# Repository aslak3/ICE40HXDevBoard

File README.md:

# ICE40HXDevBoard: an expandable iCE40HX4K development board

## Features

The specification for this development board is as follows:

* [iCE40HX4K](https://www.latticesemi.com/view_document?document_id=49312) in
144 pin QFP
  * [N25Q032A](https://docs.rs-online.com/0866/0900766b80f7f8ab.pdf) 32 Mbit SPI flash
* Space for two 5mm x 3mm oscillators
* [W9825G6KH](https://www.mouser.co.uk/datasheet/2/949/w9825g6kh_a04-1489735.pdf) 4M x 4 Banks x 16 bits SDRAM (32 MByte)
* PS/2 port with two channels for a mouse and keyboard
* I2C:
  * [DS3231M](https://www.analog.com/media/en/technical-documentation/data-sheets/ds3231m.pdf) RTC
  * [AT24C64](https://ww1.microchip.com/downloads/en/devicedoc/doc0336.pdf) EEPROM
  * Header for I2C connections
* RGB LED
* 4 buttons
* Buzzer
* [FT231XS](https://ftdichip.com/wp-content/uploads/2024/05/DS_FT231X.pdf) USB to UART converter with USB-C socket doubling up as the source of 5V power
* [MicroSDCard](https://en.wikipedia.org/wiki/SD_card) slot
* [PMOD](https://en.wikipedia.org/wiki/Pmod_Interface) header
* 40 pin expansion:
  * 3.3V and 5V power, 27 general purpose IO, 2 clock pins, shared I2C bus

A [schematic](ICE40HXDevBoard.pdf) is included here, along with the
[KiCAD](https://www.kicad.org) data files, whcih are in KiCAD 6 format.

## HDMI expansion card features

An expansion card featuring HDMI and I2S output on a 3.5mm jack has been built:

* [TFP410PAP](https://www.ti.com/lit/ds/symlink/tfp410.pdf) HDMI transmitter
  * Full size HDMI connector
* [PCM5100A](https://www.ti.com/lit/ds/symlink/pcm5100a.pdf) I2S DAC
  * 3.5mm stereo jack

## VGA expansion card features

A further, unbuilt, expansion card has been designed for VGA output:

* [ADV7123](https://www.analog.com/media/en/technical-documentation/data-sheets/ADV7123.pdf) RGB DAC
* [PCM5100A](https://www.ti.com/lit/ds/symlink/pcm5100a.pdf) I2S DAC
  * 3.5mm stereo jack

## PCB design

The PCBs are 4 layer boards.  My boards were manufactured by
[JLCPCB](https://www.jlcpcb.com).

## Using

The jumper mechanism to route the SPI signals which carry the configuration data
from the programmer was borrowed directly from the [Lattice’s iCE40 UltraPlus
Breakout Board](https://www.latticesemi.com/view_document?document_id=51987).

Any iCE40 compatible programmer should be useable. I built my own, out of a Pi
Pico, the software for which is documented in [another
repo](https://github.com/aslak3/spi-flasher). The programmer has been used to
program both the attached flash and the FPGA directly.

The header is a IDC10 in 100mil pitch. For the pinout refer to the schematic.

## Possible gotchas

The design of the FPGA board is a tweaked version of the build I have on my bench, since it has some issues:

* The PMOD pinning was backwards.
* The PS/2 port lacked clamping diodes due to the FPGA's intolerance of 5V signals from the PS/2 device. Remarkably I see no problems with my board, but it is not correct not having diodes to clamp the PS/2 data and clock lines to 3.3V.

The following features have not been tested yet:

* The MicroSDCard slot
* The SDRAM
* The I2C RTC
* The I2S DAC

## Blog

The best place to learn about this board is undoubtably [my
blog](https://www.aslak.net/).

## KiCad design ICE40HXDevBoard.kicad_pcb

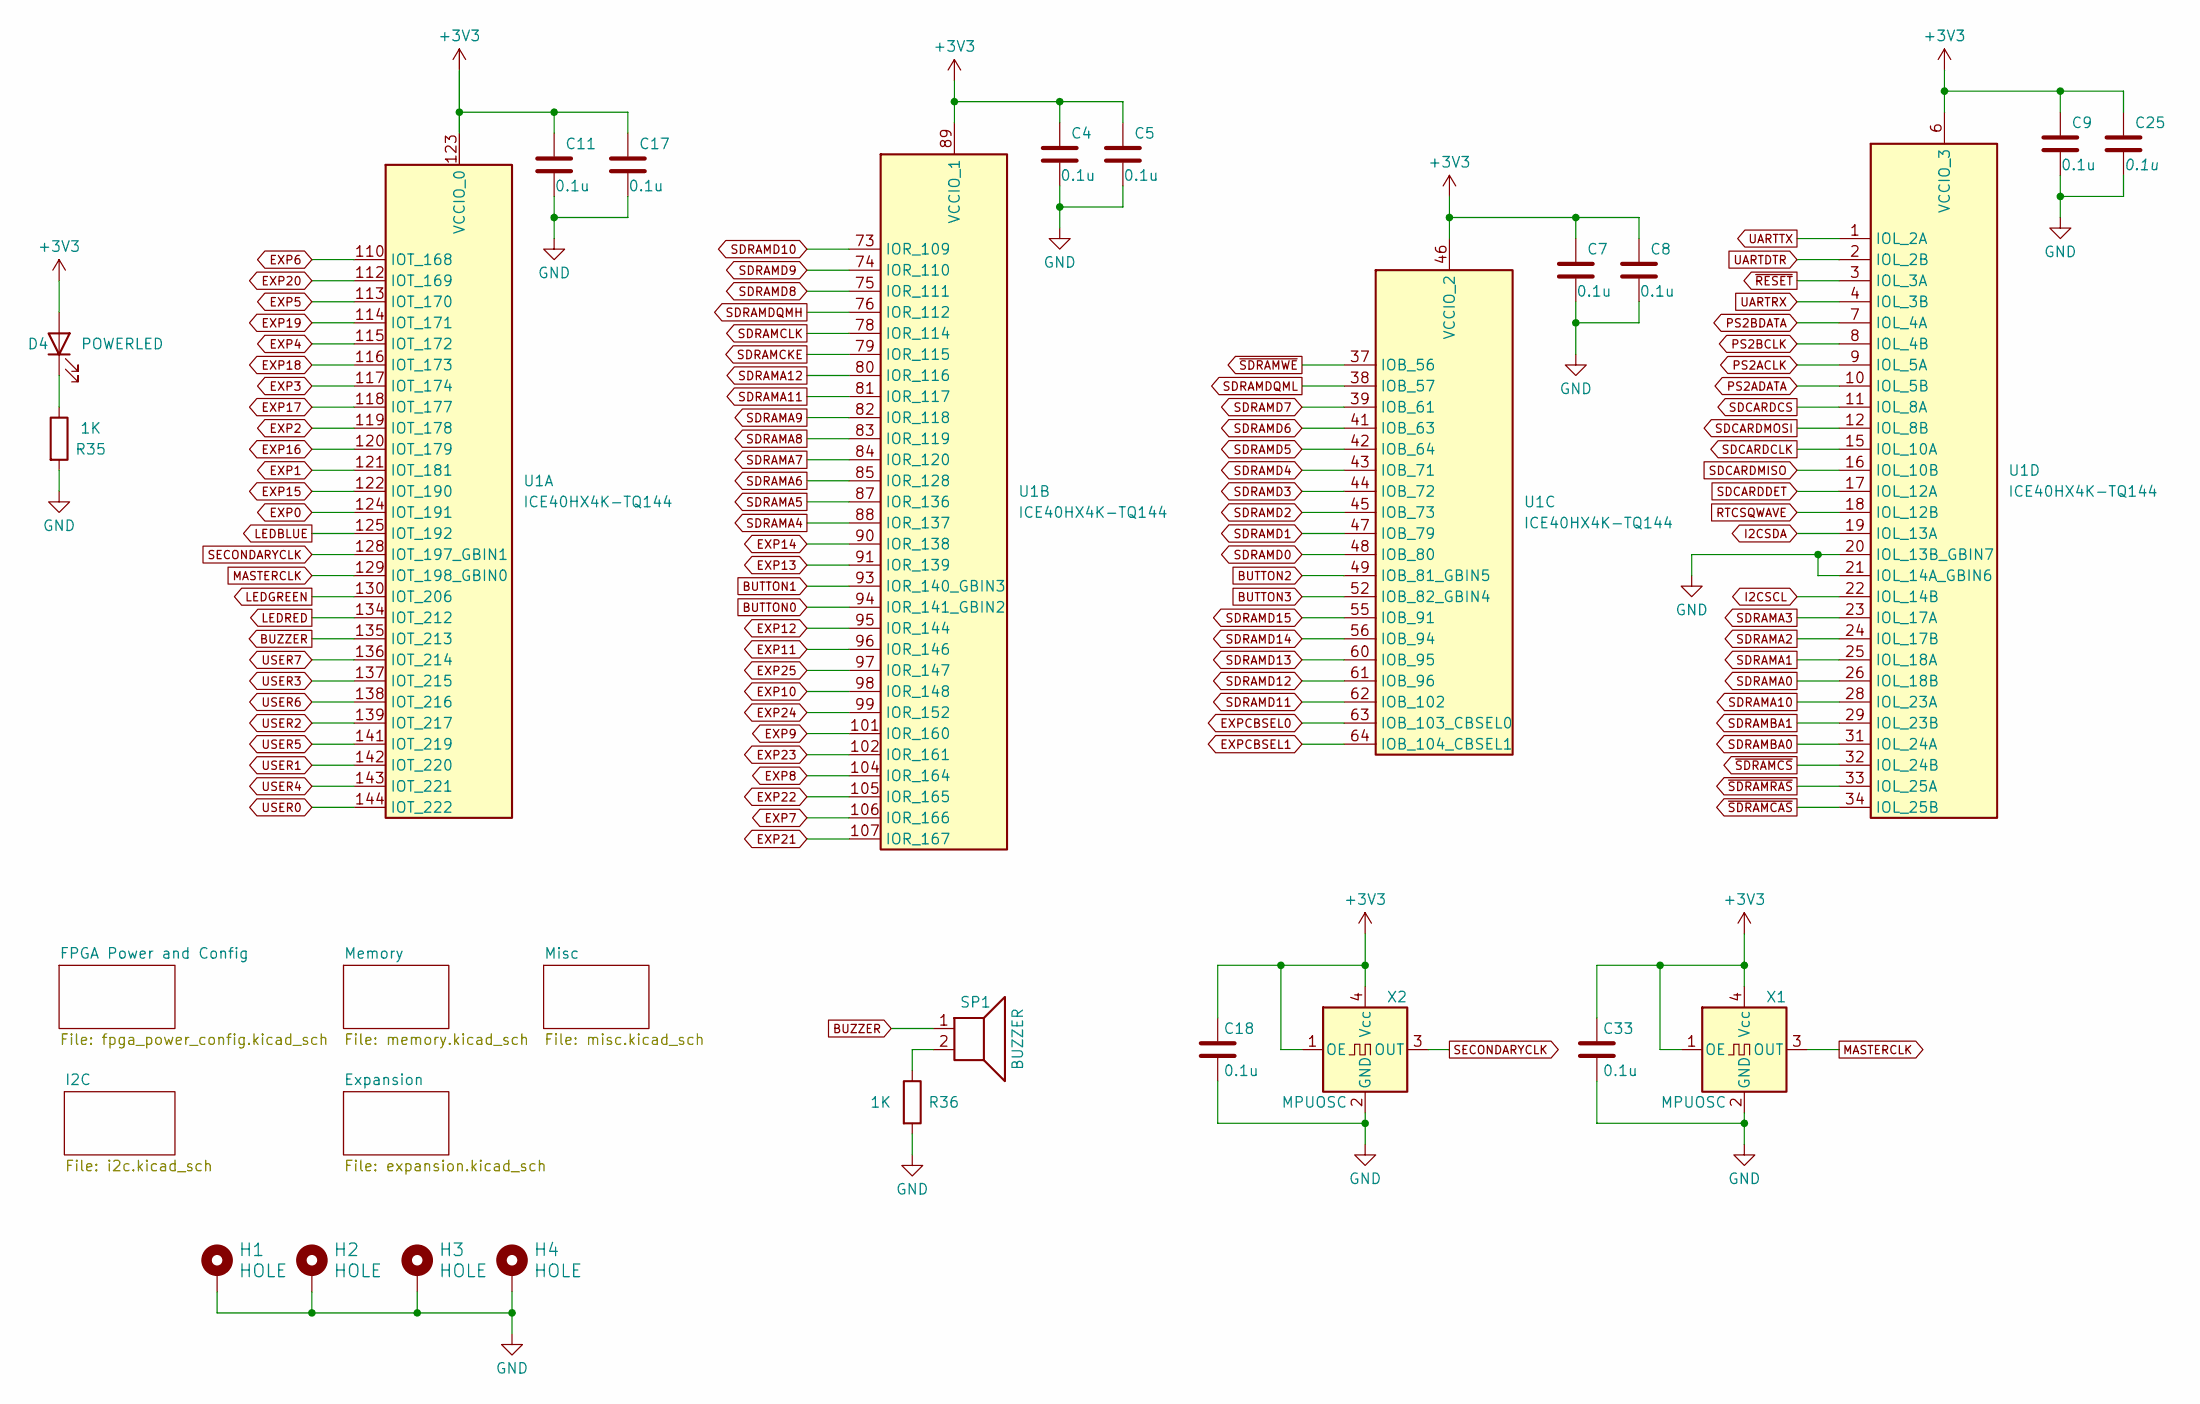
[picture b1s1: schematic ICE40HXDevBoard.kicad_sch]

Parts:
C4, C5, C7, C8, C9, C11, C17, C18, C25, C33: 0.1u; C_0805_2012Metric
D4: POWERLED; LED_1210_3225Metric
H1, H2, H3, H4: HOLE; MountingHole_3.2mm_M3_Pad
R35, R36: 1K; R_0805_2012Metric
SP1: BUZZER; Buzzer_15x7.5RM7.6
U1: ICE40HX4K-TQ144; TQFP-144_20x20mm_P0.5mm
X1, X2: MPUOSC; Oscillator_SMD_SeikoEpson_SG8002LB-4Pin_5.0x3.2mm

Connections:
+3V3: C4.1, C5.1, C7.1, C8.1, C9.1, C11.1, C17.1, C18.1, C25.1, C33.1, D4.2 (A), U1.6 (VCCIO_3), U1.30 (VCCIO_3), U1.46 (VCCIO_2), U1.57 (VCCIO_2), U1.89 (VCCIO_1), U1.100 (VCCIO_1), U1.123 (VCCIO_0), U1.131 (VCCIO_0), X1.1 (OE), X1.4 (Vcc), X2.1 (OE), X2.4 (Vcc); also elsewhere on the board
BUTTON0: U1.94 (IOR_141_GBIN2); also elsewhere on the board
BUTTON1: U1.93 (IOR_140_GBIN3); also elsewhere on the board
BUTTON2: U1.49 (IOB_81_GBIN5); also elsewhere on the board
BUTTON3: U1.52 (IOB_82_GBIN4); also elsewhere on the board
BUZZER: SP1.1, U1.135 (IOT_213)
EXP0: U1.124 (IOT_191); also elsewhere on the board
EXP1: U1.121 (IOT_181); also elsewhere on the board
EXP2: U1.119 (IOT_178); also elsewhere on the board
EXP3: U1.117 (IOT_174); also elsewhere on the board
EXP4: U1.115 (IOT_172); also elsewhere on the board
EXP5: U1.113 (IOT_170); also elsewhere on the board
EXP6: U1.110 (IOT_168); also elsewhere on the board
EXP7: U1.106 (IOR_166); also elsewhere on the board
EXP8: U1.104 (IOR_164); also elsewhere on the board
EXP9: U1.101 (IOR_160); also elsewhere on the board
EXP10: U1.98 (IOR_148); also elsewhere on the board
EXP11: U1.96 (IOR_146); also elsewhere on the board
EXP12: U1.95 (IOR_144); also elsewhere on the board
EXP13: U1.91 (IOR_139); also elsewhere on the board
EXP14: U1.90 (IOR_138); also elsewhere on the board
EXP15: U1.122 (IOT_190); also elsewhere on the board
EXP16: U1.120 (IOT_179); also elsewhere on the board
EXP17: U1.118 (IOT_177); also elsewhere on the board
EXP18: U1.116 (IOT_173); also elsewhere on the board
EXP19: U1.114 (IOT_171); also elsewhere on the board
EXP20: U1.112 (IOT_169); also elsewhere on the board
EXP21: U1.107 (IOR_167); also elsewhere on the board
EXP22: U1.105 (IOR_165); also elsewhere on the board
EXP23: U1.102 (IOR_161); also elsewhere on the board
EXP24: U1.99 (IOR_152); also elsewhere on the board
EXP25: U1.97 (IOR_147); also elsewhere on the board
EXPCBSEL0: U1.63 (IOB_103_CBSEL0); also elsewhere on the board
EXPCBSEL1: U1.64 (IOB_104_CBSEL1); also elsewhere on the board
GND: C4.2, C5.2, C7.2, C8.2, C9.2, C11.2, C17.2, C18.2, C25.2, C33.2, H1.1, H2.1, H3.1, H4.1, R35.2, R36.2, U1.20 (IOL_13B_GBIN7), U1.21 (IOL_14A_GBIN6), X1.2 (GND), X2.2 (GND); also elsewhere on the board
I2CSCL: U1.22 (IOL_14B); also elsewhere on the board
I2CSDA: U1.19 (IOL_13A); also elsewhere on the board
LEDBLUE: U1.125 (IOT_192); also elsewhere on the board
LEDGREEN: U1.130 (IOT_206); also elsewhere on the board
LEDRED: U1.134 (IOT_212); also elsewhere on the board
MASTERCLK: U1.129 (IOT_198_GBIN0), X1.3 (OUT); also elsewhere on the board
unnamed: D4.1 (K), R35.1
unnamed: R36.1, SP1.2
PS2ACLK: U1.9 (IOL_5A); also elsewhere on the board
PS2ADATA: U1.10 (IOL_5B); also elsewhere on the board
PS2BCLK: U1.8 (IOL_4B); also elsewhere on the board
PS2BDATA: U1.7 (IOL_4A); also elsewhere on the board
RTCSQWAVE: U1.18 (IOL_12B); also elsewhere on the board
SDCARDCLK: U1.15 (IOL_10A); also elsewhere on the board
SDCARDCS: U1.11 (IOL_8A); also elsewhere on the board
SDCARDDET: U1.17 (IOL_12A); also elsewhere on the board
SDCARDMISO: U1.16 (IOL_10B); also elsewhere on the board
SDCARDMOSI: U1.12 (IOL_8B); also elsewhere on the board
SDRAMA0: U1.26 (IOL_18B); also elsewhere on the board
SDRAMA1: U1.25 (IOL_18A); also elsewhere on the board
SDRAMA2: U1.24 (IOL_17B); also elsewhere on the board
SDRAMA3: U1.23 (IOL_17A); also elsewhere on the board
SDRAMA4: U1.88 (IOR_137); also elsewhere on the board
SDRAMA5: U1.87 (IOR_136); also elsewhere on the board
SDRAMA6: U1.85 (IOR_128); also elsewhere on the board
SDRAMA7: U1.84 (IOR_120); also elsewhere on the board
SDRAMA8: U1.83 (IOR_119); also elsewhere on the board
SDRAMA9: U1.82 (IOR_118); also elsewhere on the board
SDRAMA10: U1.28 (IOL_23A); also elsewhere on the board
SDRAMA11: U1.81 (IOR_117); also elsewhere on the board
SDRAMA12: U1.80 (IOR_116); also elsewhere on the board
SDRAMBA0: U1.31 (IOL_24A); also elsewhere on the board
SDRAMBA1: U1.29 (IOL_23B); also elsewhere on the board
SDRAMCKE: U1.79 (IOR_115); also elsewhere on the board
SDRAMCLK: U1.78 (IOR_114); also elsewhere on the board
SDRAMD0: U1.48 (IOB_80); also elsewhere on the board
SDRAMD1: U1.47 (IOB_79); also elsewhere on the board
SDRAMD2: U1.45 (IOB_73); also elsewhere on the board
SDRAMD3: U1.44 (IOB_72); also elsewhere on the board
SDRAMD4: U1.43 (IOB_71); also elsewhere on the board
SDRAMD5: U1.42 (IOB_64); also elsewhere on the board
SDRAMD6: U1.41 (IOB_63); also elsewhere on the board
SDRAMD7: U1.39 (IOB_61); also elsewhere on the board
SDRAMD8: U1.75 (IOR_111); also elsewhere on the board
SDRAMD9: U1.74 (IOR_110); also elsewhere on the board
SDRAMD10: U1.73 (IOR_109); also elsewhere on the board
SDRAMD11: U1.62 (IOB_102); also elsewhere on the board
SDRAMD12: U1.61 (IOB_96); also elsewhere on the board
SDRAMD13: U1.60 (IOB_95); also elsewhere on the board
SDRAMD14: U1.56 (IOB_94); also elsewhere on the board
SDRAMD15: U1.55 (IOB_91); also elsewhere on the board
SDRAMDQMH: U1.76 (IOR_112); also elsewhere on the board
SDRAMDQML: U1.38 (IOB_57); also elsewhere on the board
SECONDARYCLK: U1.128 (IOT_197_GBIN1), X2.3 (OUT); also elsewhere on the board
UARTDTR: U1.2 (IOL_2B); also elsewhere on the board
UARTRX: U1.4 (IOL_3B); also elsewhere on the board
UARTTX: U1.1 (IOL_2A); also elsewhere on the board
USER0: U1.144 (IOT_222); also elsewhere on the board
USER1: U1.142 (IOT_220); also elsewhere on the board
USER2: U1.139 (IOT_217); also elsewhere on the board
USER3: U1.137 (IOT_215); also elsewhere on the board
USER4: U1.143 (IOT_221); also elsewhere on the board
USER5: U1.141 (IOT_219); also elsewhere on the board
USER6: U1.138 (IOT_216); also elsewhere on the board
USER7: U1.136 (IOT_214); also elsewhere on the board
~RESET: U1.3 (IOL_3A); also elsewhere on the board
~SDRAMCAS: U1.34 (IOL_25B); also elsewhere on the board
~SDRAMCS: U1.32 (IOL_24B); also elsewhere on the board
~SDRAMRAS: U1.33 (IOL_25A); also elsewhere on the board
~SDRAMWE: U1.37 (IOB_56); also elsewhere on the board

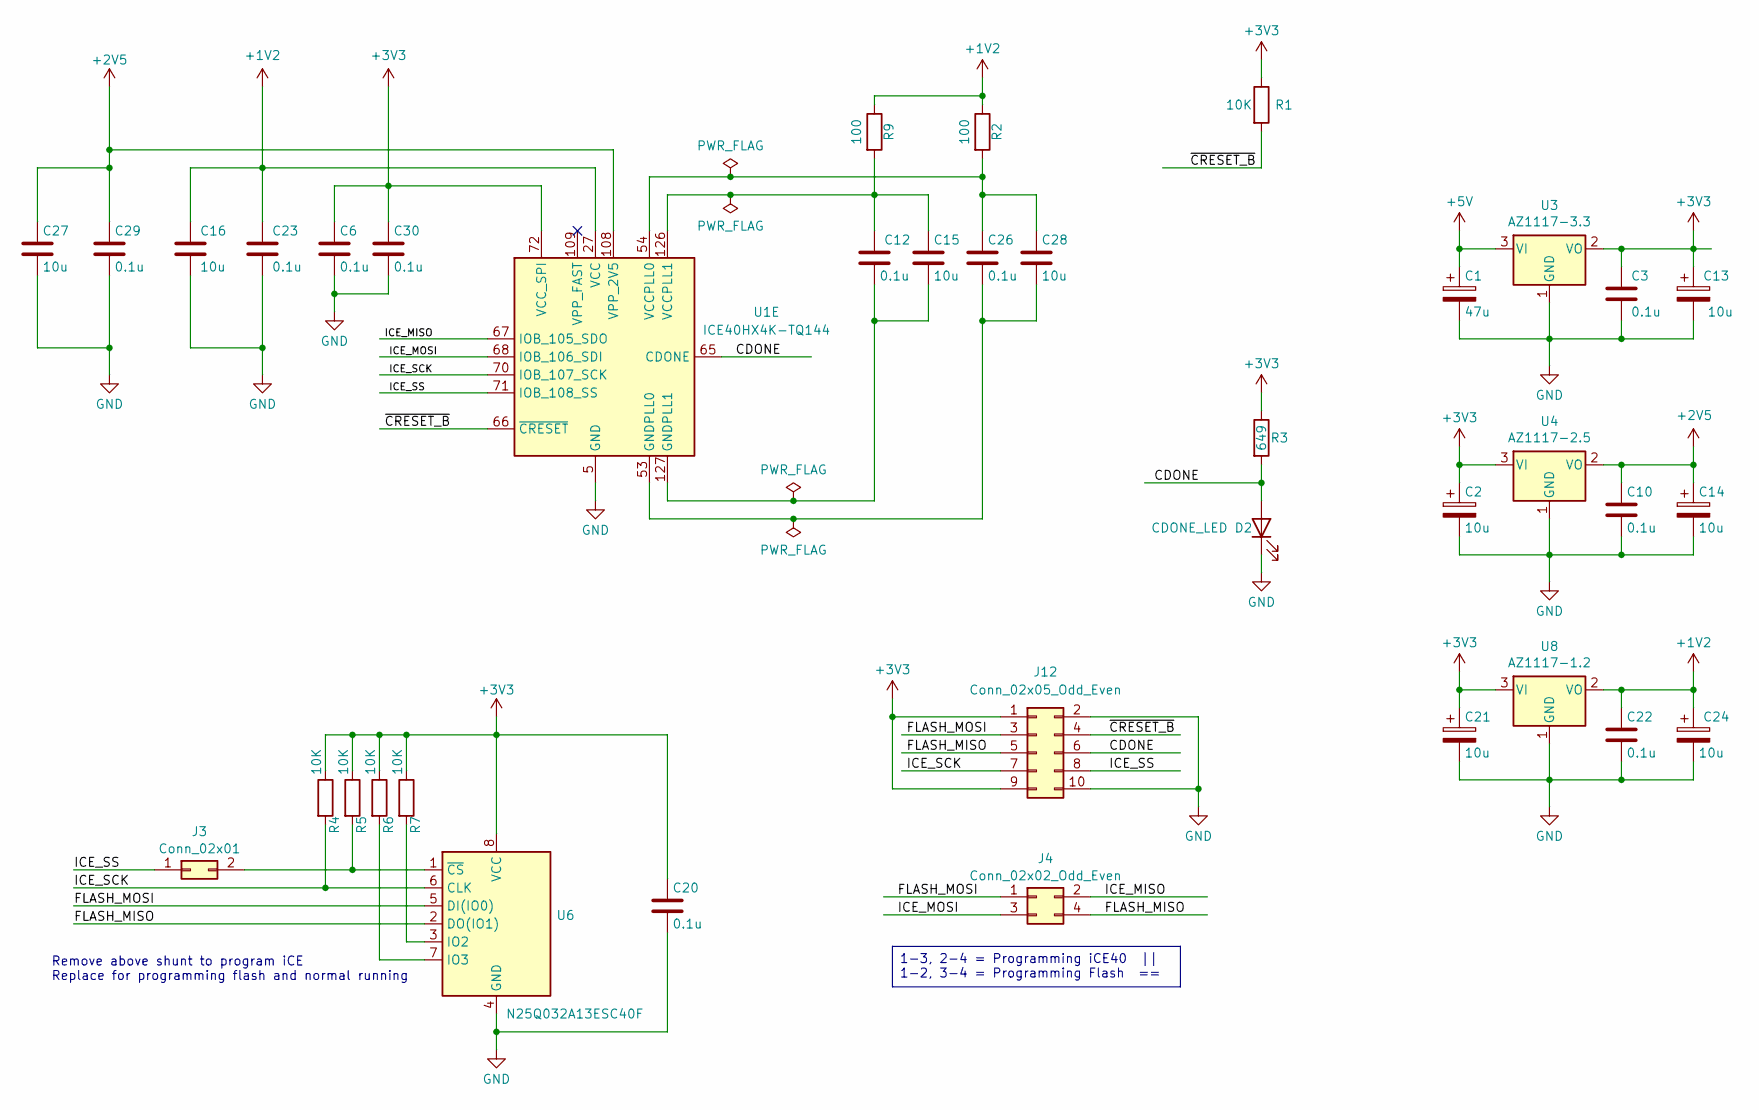
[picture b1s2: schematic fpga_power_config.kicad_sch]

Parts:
C1: 47u; CP_EIA-7343-15_Kemet-W
C2, C13, C14, C21, C24: 10u; CP_EIA-3216-10_Kemet-I
C3, C6, C10, C12, C20, C22, C23, C26, C29, C30: 0.1u; C_0805_2012Metric
C15, C16, C27, C28: 10u; C_0805_2012Metric
D2: CDONE_LED; LED_1210_3225Metric
J3: Conn_02x01; PinHeader_2x01_P2.54mm_Vertical
J4: Conn_02x02_Odd_Even; PinHeader_2x02_P2.54mm_Vertical
J12: Conn_02x05_Odd_Even; IDC-Header_2x05_P2.54mm_Vertical
R1, R4, R5, R6, R7: 10K; R_0805_2012Metric
R2, R9: 100; R_0805_2012Metric
R3: 649; R_0805_2012Metric
U1: ICE40HX4K-TQ144; TQFP-144_20x20mm_P0.5mm
U3: AZ1117-3.3; SOT-223-3_TabPin2
U4: AZ1117-2.5; SOT-223-3_TabPin2
U6: N25Q032A13ESC40F; SOP-8_3.9x4.9mm_P1.27mm
U8: AZ1117-1.2; SOT-223-3_TabPin2

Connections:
+1V2: C16.1, C22.1, C23.1, C24.1, R2.1, R9.1, U1.27 (VCC), U1.40 (VCC), U1.92 (VCC), U1.111 (VCC), U8.2 (VO)
+2V5: C10.1, C14.1, C27.1, C29.1, U1.108 (VPP_2V5), U4.2 (VO)
+3V3: C2.1, C3.1, C6.1, C13.1, C20.1, C21.1, C30.1, J12.1, J12.9, R1.1, R3.1, R4.1, R5.1, R6.1, R7.1, U1.72 (VCC_SPI), U3.2 (VO), U4.3 (VI), U6.8 (VCC), U8.3 (VI); also elsewhere on the board
+5V: C1.1, U3.3 (VI); also elsewhere on the board
/FPGA Power and Config/CDONE: D2.2 (A), J12.6, R3.2, U1.65 (CDONE)
/FPGA Power and Config/FLASH_MISO: J4.4, J12.5, U6.2 (DO(IO1))
/FPGA Power and Config/FLASH_MOSI: J4.1, J12.3, U6.5 (DI(IO0))
/FPGA Power and Config/ICE_MISO: J4.2, U1.67 (IOB_105_SDO)
/FPGA Power and Config/ICE_MOSI: J4.3, U1.68 (IOB_106_SDI)
/FPGA Power and Config/ICE_SCK: J12.7, R4.2, U1.70 (IOB_107_SCK), U6.6 (CLK)
/FPGA Power and Config/ICE_SS: J3.1, J12.8, U1.71 (IOB_108_SS)
/FPGA Power and Config/~CRESET_B: J12.4, R1.2, U1.66 (~CRESET)
GND: C1.2, C2.2, C3.2, C6.2, C10.2, C13.2, C14.2, C16.2, C20.2, C21.2, C22.2, C23.2, C24.2, C27.2, C29.2, C30.2, D2.1 (K), J12.2, J12.10, U1.5 (GND), U1.13 (GND), U1.14 (GND), U1.59 (GND), U1.69 (GND), U1.86 (GND), U1.103 (GND), U1.132 (GND), U1.140 (GND), U3.1 (GND), U4.1 (GND), U6.4 (GND), U8.1 (GND); also elsewhere on the board
unnamed: J3.2, R5.2, U6.1 (~CS)
unnamed: C26.2, C28.2, U1.53 (GNDPLL0)
unnamed: C12.2, C15.2, U1.127 (GNDPLL1)
unnamed: C26.1, C28.1, R2.2, U1.54 (VCCPLL0)
unnamed: C12.1, C15.1, R9.2, U1.126 (VCCPLL1)
unnamed: R7.2, U6.3 (IO2)
unnamed: R6.2, U6.7 (IO3)

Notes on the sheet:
Remove above shunt to program iCE Replace for programming flash and normal running
1-3, 2-4 = Programming iCE40 || 1-2, 3-4 = Programming Flash ==

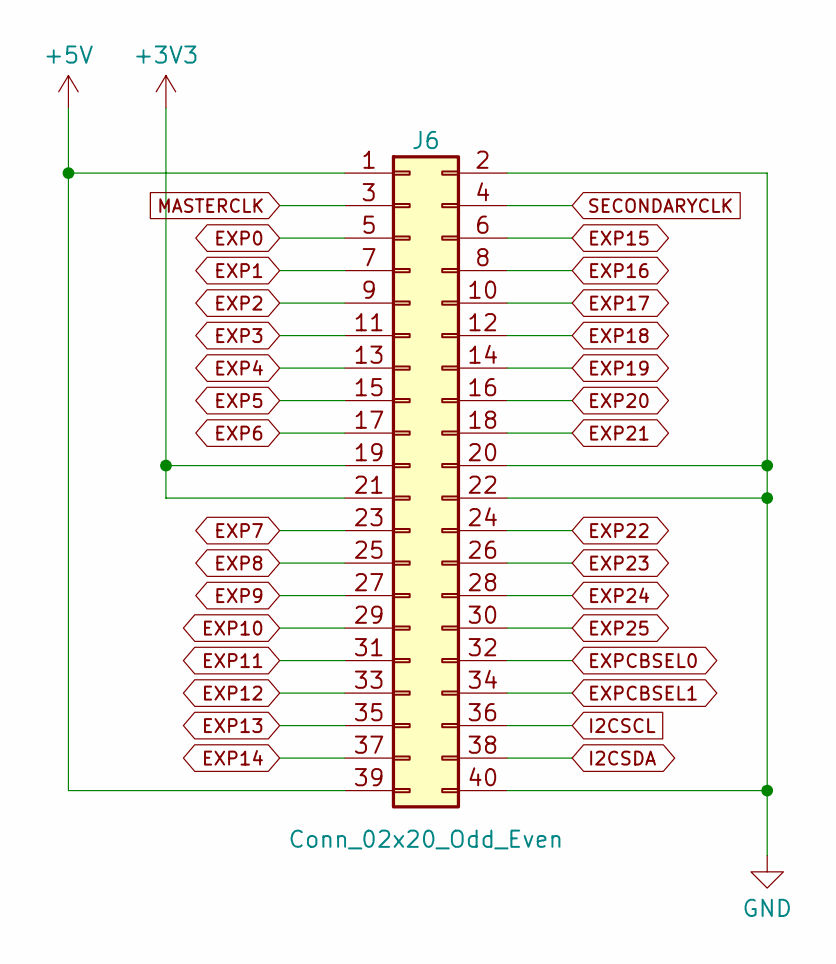
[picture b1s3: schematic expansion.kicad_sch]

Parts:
J6: Conn_02x20_Odd_Even; PinHeader_2x20_P2.54mm_Horizontal

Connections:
+3V3: J6.19, J6.21; also elsewhere on the board
+5V: J6.1, J6.39; also elsewhere on the board
EXP0: J6.5; also elsewhere on the board
EXP1: J6.7; also elsewhere on the board
EXP2: J6.9; also elsewhere on the board
EXP3: J6.11; also elsewhere on the board
EXP4: J6.13; also elsewhere on the board
EXP5: J6.15; also elsewhere on the board
EXP6: J6.17; also elsewhere on the board
EXP7: J6.23; also elsewhere on the board
EXP8: J6.25; also elsewhere on the board
EXP9: J6.27; also elsewhere on the board
EXP10: J6.29; also elsewhere on the board
EXP11: J6.31; also elsewhere on the board
EXP12: J6.33; also elsewhere on the board
EXP13: J6.35; also elsewhere on the board
EXP14: J6.37; also elsewhere on the board
EXP15: J6.6; also elsewhere on the board
EXP16: J6.8; also elsewhere on the board
EXP17: J6.10; also elsewhere on the board
EXP18: J6.12; also elsewhere on the board
EXP19: J6.14; also elsewhere on the board
EXP20: J6.16; also elsewhere on the board
EXP21: J6.18; also elsewhere on the board
EXP22: J6.24; also elsewhere on the board
EXP23: J6.26; also elsewhere on the board
EXP24: J6.28; also elsewhere on the board
EXP25: J6.30; also elsewhere on the board
EXPCBSEL0: J6.32; also elsewhere on the board
EXPCBSEL1: J6.34; also elsewhere on the board
GND: J6.2, J6.20, J6.22, J6.40; also elsewhere on the board
I2CSCL: J6.36; also elsewhere on the board
I2CSDA: J6.38; also elsewhere on the board
MASTERCLK: J6.3; also elsewhere on the board
SECONDARYCLK: J6.4; also elsewhere on the board

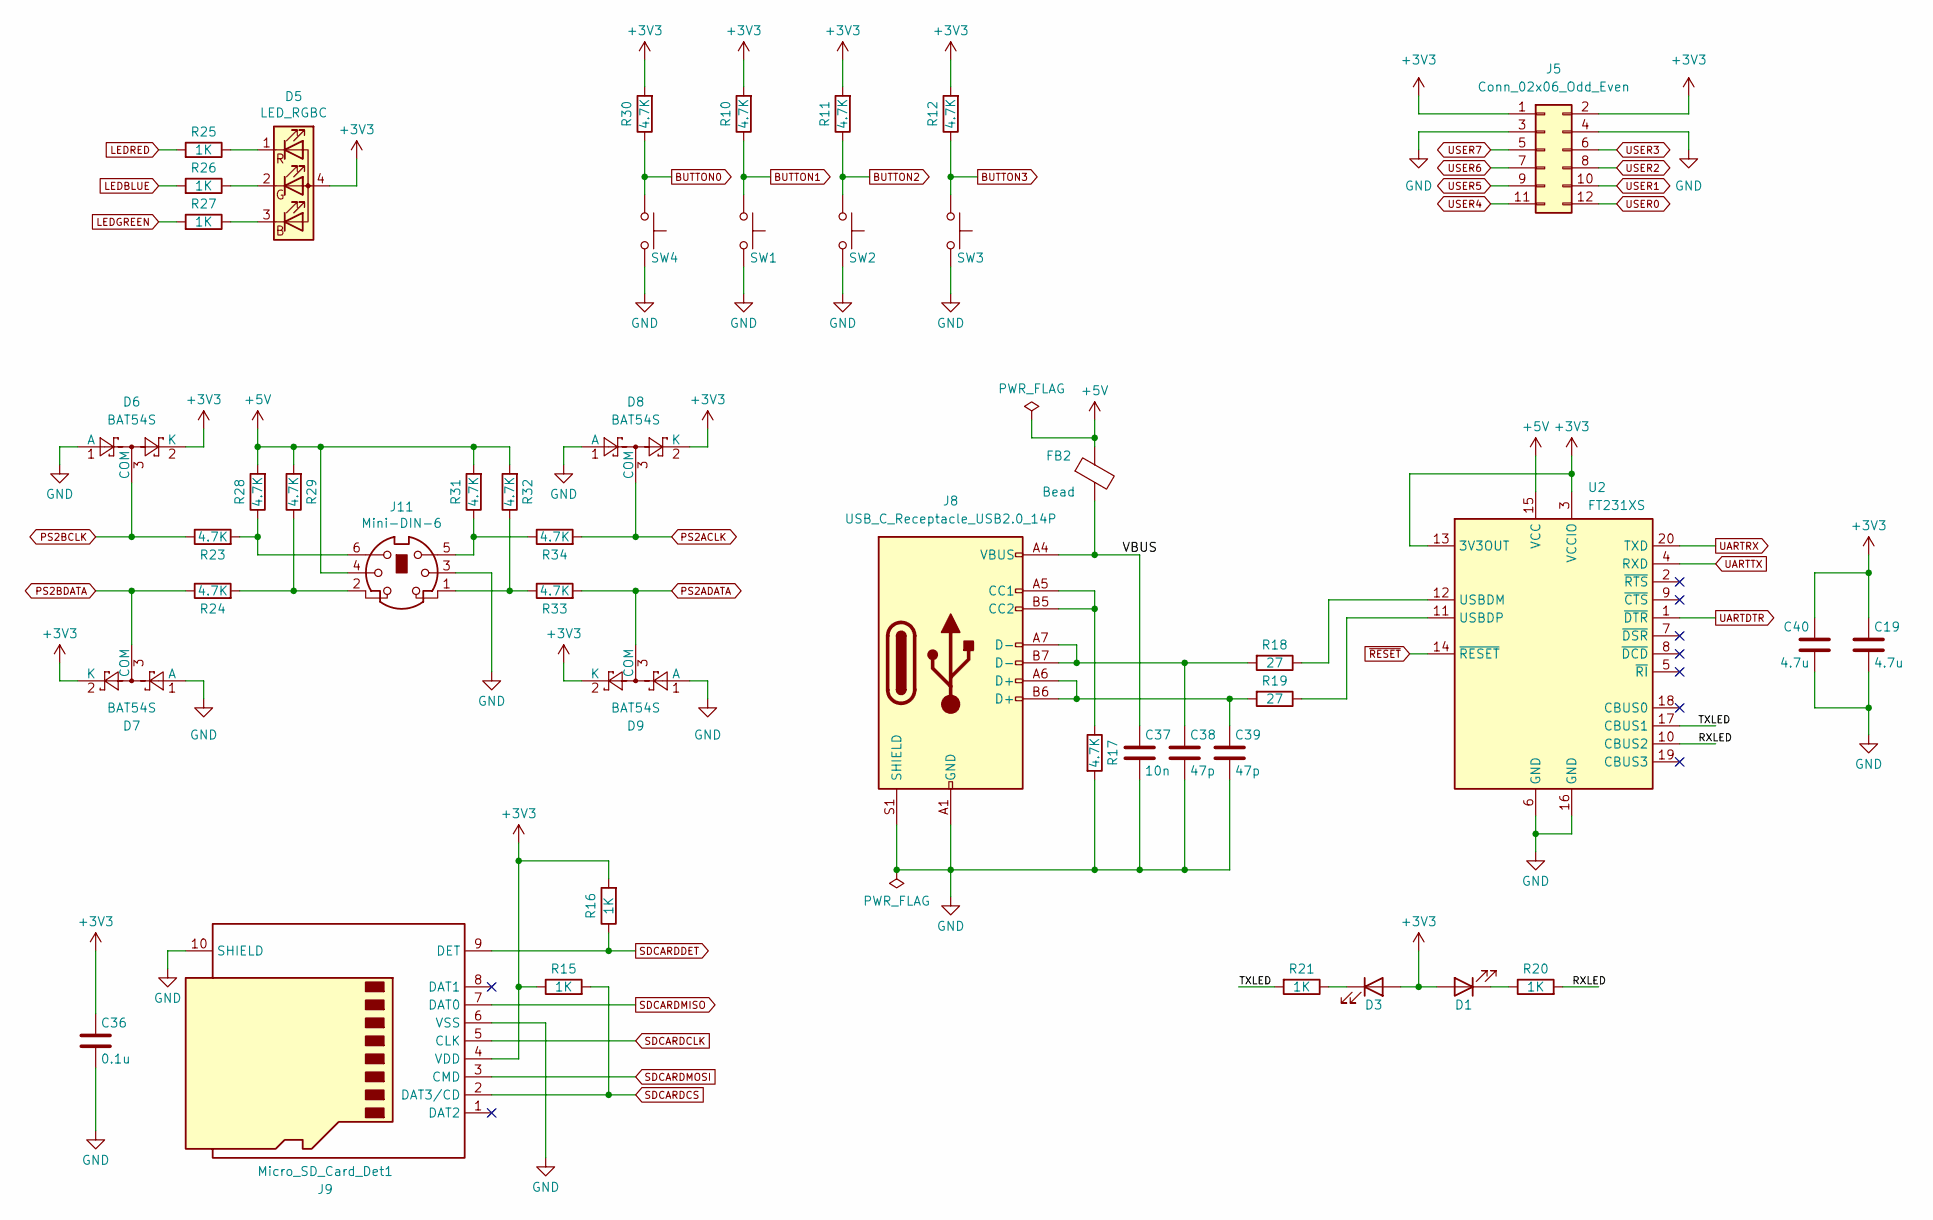
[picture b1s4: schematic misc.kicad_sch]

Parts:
C19, C40: 4.7u; C_0805_2012Metric
C36: 0.1u; C_0805_2012Metric
C37: 10n; C_0805_2012Metric
C38, C39: 47p; C_0805_2012Metric
D1, D3: UART_LED; LED_1210_3225Metric
D5: LED_RGBC; LED_Cree-PLCC4_3.2x2.8mm_CCW
D6, D7, D8, D9: BAT54S; SOT-23
FB2: Bead; L_1206_3216Metric
J5: Conn_02x06_Odd_Even; PinSocket_2x06_P2.54mm_Horizontal
J8: USB_C_Receptacle_USB2.0_14P; USB_C_Receptacle_GCT_USB4105-xx-A_16P_TopMnt_Horizontal
J9: Micro_SD_Card_Det1; microSD_HC_Hirose_DM3BT-DSF-PEJS
J11: Mini-DIN-6; Connector_Mini-DIN_Female_6Pin_2rows
R10, R11, R12, R17, R23, R24, R28, R29, R30, R31, R32, R33, R34: 4.7K; R_0805_2012Metric
R15, R16, R20, R21, R25, R26, R27: 1K; R_0805_2012Metric
R18, R19: 27; R_0805_2012Metric
SW1, SW2, SW3, SW4: BUTTON; SW_Push_1P1T_NO_CK_KSC6xxJ
U2: FT231XS; SSOP-20_3.9x8.7mm_P0.635mm

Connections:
+3V3: C19.1, C36.1, C40.1, D1.2 (A), D3.2 (A), D5.4 (A), D6.2 (K), D7.2 (K), D8.2 (K), D9.2 (K), J5.1, J5.2, J9.4 (VDD), R10.2, R11.2, R12.2, R15.1, R16.2, R30.2, U2.3 (VCCIO), U2.13 (3V3OUT); also elsewhere on the board
+5V: FB2.1, J11.4, R28.2, R29.2, R31.2, R32.2, U2.15 (VCC); also elsewhere on the board
/Misc/RXLED: R20.2, U2.10 (CBUS2)
/Misc/TXLED: R21.2, U2.17 (CBUS1)
/Misc/VBUS: C37.1, FB2.2, J8.A4 (VBUS), J8.A9 (VBUS), J8.B4 (VBUS), J8.B9 (VBUS)
BUTTON0: R30.1, SW4.1; also elsewhere on the board
BUTTON1: R10.1, SW1.1; also elsewhere on the board
BUTTON2: R11.1, SW2.1; also elsewhere on the board
BUTTON3: R12.1, SW3.1; also elsewhere on the board
GND: C19.2, C36.2, C37.2, C38.2, C39.2, C40.2, D6.1 (A), D7.1 (A), D8.1 (A), D9.1 (A), J5.3, J5.4, J8.A1 (GND), J8.A12 (GND), J8.B1 (GND), J8.B12 (GND), J8.S1 (SHIELD), J9.6 (VSS), J9.10 (SHIELD), J11.3, R17.2, SW1.2, SW2.2, SW3.2, SW4.2, U2.6 (GND), U2.16 (GND); also elsewhere on the board
LEDBLUE: R26.2; also elsewhere on the board
LEDGREEN: R27.2; also elsewhere on the board
LEDRED: R25.2; also elsewhere on the board
unnamed: C38.1, J8.A7 (D-), J8.B7 (D-), R18.2
unnamed: C39.1, J8.A6 (D+), J8.B6 (D+), R19.2
unnamed: D1.1 (K), R20.1
unnamed: D3.1 (K), R21.1
unnamed: D5.3 (BK), R27.1
unnamed: D5.2 (GK), R26.1
unnamed: D5.1 (RK), R25.1
unnamed: J8.A5 (CC1), J8.B5 (CC2), R17.1
unnamed: J11.1, R32.1, R33.1
unnamed: J11.2, R24.2, R29.1
unnamed: J11.5, R31.1, R34.1
unnamed: J11.6, R23.2, R28.1
unnamed: R18.1, U2.12 (USBDM)
unnamed: R19.1, U2.11 (USBDP)
PS2ACLK: D8.3 (COM), R34.2; also elsewhere on the board
PS2ADATA: D9.3 (COM), R33.2; also elsewhere on the board
PS2BCLK: D6.3 (COM), R23.1; also elsewhere on the board
PS2BDATA: D7.3 (COM), R24.1; also elsewhere on the board
SDCARDCLK: J9.5 (CLK); also elsewhere on the board
SDCARDCS: J9.2 (DAT3/CD), R15.2; also elsewhere on the board
SDCARDDET: J9.9 (DET), R16.1; also elsewhere on the board
SDCARDMISO: J9.7 (DAT0); also elsewhere on the board
SDCARDMOSI: J9.3 (CMD); also elsewhere on the board
UARTDTR: U2.1 (~DTR); also elsewhere on the board
UARTRX: U2.20 (TXD); also elsewhere on the board
UARTTX: U2.4 (RXD); also elsewhere on the board
USER0: J5.12; also elsewhere on the board
USER1: J5.10; also elsewhere on the board
USER2: J5.8; also elsewhere on the board
USER3: J5.6; also elsewhere on the board
USER4: J5.11; also elsewhere on the board
USER5: J5.9; also elsewhere on the board
USER6: J5.7; also elsewhere on the board
USER7: J5.5; also elsewhere on the board
~RESET: U2.14 (~RESET); also elsewhere on the board

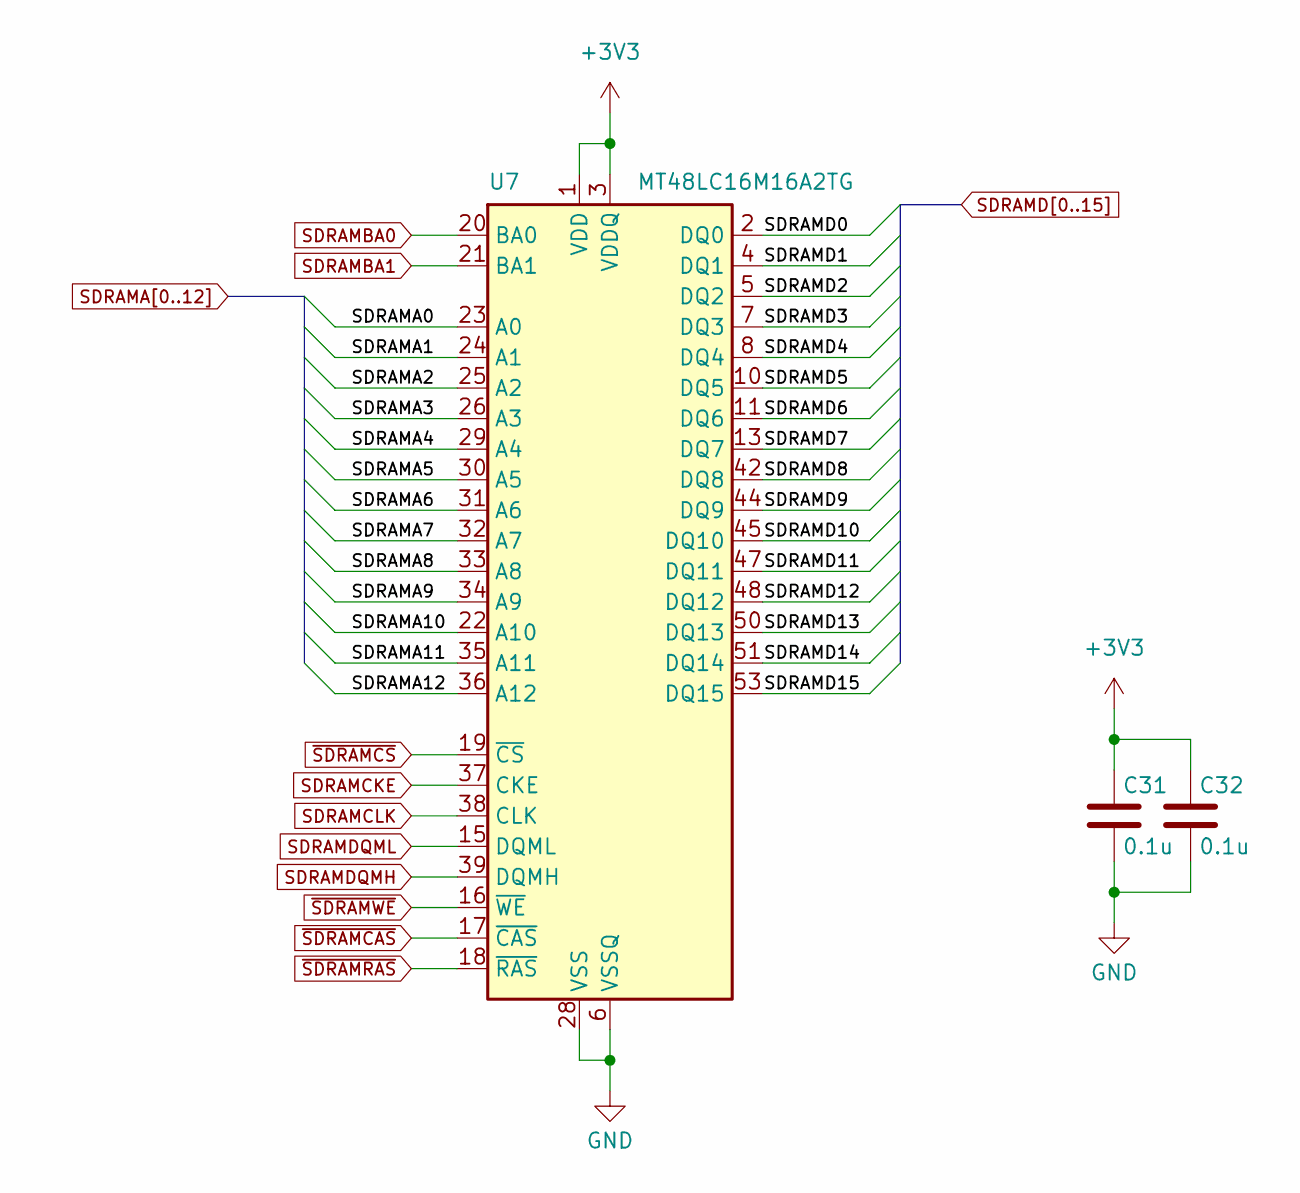
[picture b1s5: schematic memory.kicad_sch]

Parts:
C31, C32: 0.1u; C_0805_2012Metric
U7: MT48LC16M16A2TG; TSOP-II-54_22.2x10.16mm_P0.8mm

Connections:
+3V3: C31.1, C32.1, U7.1 (VDD), U7.3 (VDDQ), U7.9 (VDDQ), U7.14 (VDD), U7.27 (VDD), U7.43 (VDDQ), U7.49 (VDDQ); also elsewhere on the board
GND: C31.2, C32.2, U7.6 (VSSQ), U7.12 (VSSQ), U7.28 (VSS), U7.41 (VSS), U7.46 (VSSQ), U7.52 (VSSQ), U7.54 (VSS); also elsewhere on the board
SDRAMA0: U7.23 (A0); also elsewhere on the board
SDRAMA1: U7.24 (A1); also elsewhere on the board
SDRAMA2: U7.25 (A2); also elsewhere on the board
SDRAMA3: U7.26 (A3); also elsewhere on the board
SDRAMA4: U7.29 (A4); also elsewhere on the board
SDRAMA5: U7.30 (A5); also elsewhere on the board
SDRAMA6: U7.31 (A6); also elsewhere on the board
SDRAMA7: U7.32 (A7); also elsewhere on the board
SDRAMA8: U7.33 (A8); also elsewhere on the board
SDRAMA9: U7.34 (A9); also elsewhere on the board
SDRAMA10: U7.22 (A10); also elsewhere on the board
SDRAMA11: U7.35 (A11); also elsewhere on the board
SDRAMA12: U7.36 (A12); also elsewhere on the board
SDRAMBA0: U7.20 (BA0); also elsewhere on the board
SDRAMBA1: U7.21 (BA1); also elsewhere on the board
SDRAMCKE: U7.37 (CKE); also elsewhere on the board
SDRAMCLK: U7.38 (CLK); also elsewhere on the board
SDRAMD0: U7.2 (DQ0); also elsewhere on the board
SDRAMD1: U7.4 (DQ1); also elsewhere on the board
SDRAMD2: U7.5 (DQ2); also elsewhere on the board
SDRAMD3: U7.7 (DQ3); also elsewhere on the board
SDRAMD4: U7.8 (DQ4); also elsewhere on the board
SDRAMD5: U7.10 (DQ5); also elsewhere on the board
SDRAMD6: U7.11 (DQ6); also elsewhere on the board
SDRAMD7: U7.13 (DQ7); also elsewhere on the board
SDRAMD8: U7.42 (DQ8); also elsewhere on the board
SDRAMD9: U7.44 (DQ9); also elsewhere on the board
SDRAMD10: U7.45 (DQ10); also elsewhere on the board
SDRAMD11: U7.47 (DQ11); also elsewhere on the board
SDRAMD12: U7.48 (DQ12); also elsewhere on the board
SDRAMD13: U7.50 (DQ13); also elsewhere on the board
SDRAMD14: U7.51 (DQ14); also elsewhere on the board
SDRAMD15: U7.53 (DQ15); also elsewhere on the board
SDRAMDQMH: U7.39 (DQMH); also elsewhere on the board
SDRAMDQML: U7.15 (DQML); also elsewhere on the board
~SDRAMCAS: U7.17 (~CAS); also elsewhere on the board
~SDRAMCS: U7.19 (~CS); also elsewhere on the board
~SDRAMRAS: U7.18 (~RAS); also elsewhere on the board
~SDRAMWE: U7.16 (~WE); also elsewhere on the board

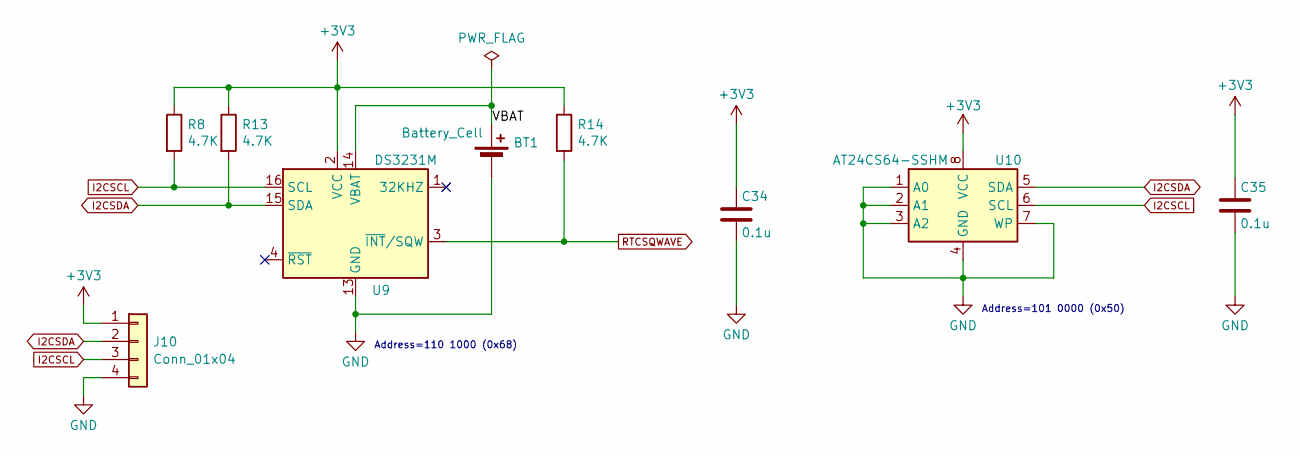
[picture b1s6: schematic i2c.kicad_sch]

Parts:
BT1: Battery_Cell; BatteryHolder_Keystone_3000_1x12mm
C34, C35: 0.1u; C_0805_2012Metric
J10: Conn_01x04; PinHeader_1x04_P2.54mm_Vertical
R8, R13, R14: 4.7K; R_0805_2012Metric
U9: DS3231M; SOIC-16W_7.5x10.3mm_P1.27mm
U10: AT24CS64-SSHM; SOIC-8_3.9x4.9mm_P1.27mm

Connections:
+3V3: C34.1, C35.1, J10.1, R8.1, R13.1, R14.1, U9.2 (VCC), U10.8 (VCC); also elsewhere on the board
/I2C/VBAT: BT1.1 (+), U9.14 (VBAT)
GND: BT1.2 (-), C34.2, C35.2, J10.4, U9.5 (GND), U9.6 (GND), U9.7 (GND), U9.8 (GND), U9.9 (GND), U9.10 (GND), U9.11 (GND), U9.12 (GND), U9.13 (GND), U10.1 (A0), U10.2 (A1), U10.3 (A2), U10.4 (GND), U10.7 (WP); also elsewhere on the board
I2CSCL: J10.3, R8.2, U9.16 (SCL), U10.6 (SCL); also elsewhere on the board
I2CSDA: J10.2, R13.2, U9.15 (SDA), U10.5 (SDA); also elsewhere on the board
RTCSQWAVE: R14.2, U9.3 (~INT/SQW); also elsewhere on the board

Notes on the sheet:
Address=110 1000 (0x68)
Address=101 0000 (0x50)

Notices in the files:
ExpansionCards/ICE40HXDevBoardHDMI/ICE40HXDevBoardHDMI.kicad_pcb:
© 2025-02-21
ICE40HXDevBoard.kicad_pcb:
© 2025-07-26
